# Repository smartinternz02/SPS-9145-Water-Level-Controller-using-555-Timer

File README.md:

# SPS-9145-Water-Level-Controller-using-555-Timer
Water Level Controller using 555 Timer

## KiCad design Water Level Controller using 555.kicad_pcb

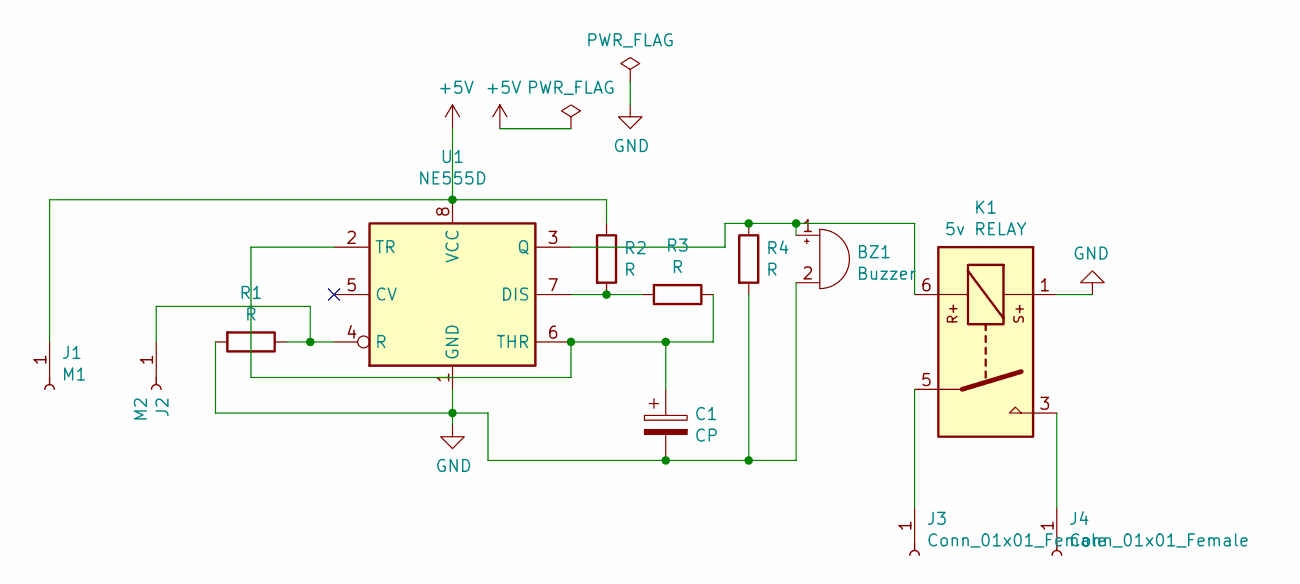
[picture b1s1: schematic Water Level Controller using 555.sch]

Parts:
BZ1: Buzzer; MagneticBuzzer_Kingstate_KCG0601
C1: CP; CP_Radial_D5.0mm_P2.50mm
J1: M1; Banana_Jack_1Pin
J2: M2; Banana_Jack_1Pin
J3, J4: Conn_01x01_Female; Banana_Jack_1Pin
K1: 5v RELAY; Relay_1P1T_NO_10x24x18.8mm_Panasonic_ADW11xxxxW_THT
R1, R2, R3, R4: R; R_Axial_DIN0207_L6.3mm_D2.5mm_P10.16mm_Horizontal
U1: NE555D; SOIC-8_3.9x4.9mm_P1.27mm

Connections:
+5V: J1.1, R2.1, U1.8 (VCC)
GND: BZ1.2 (+), C1.2, K1.1, R1.2, R4.2, U1.1 (GND)
unnamed: BZ1.1 (-), K1.6, R4.1, U1.3 (Q)
unnamed: C1.1, R3.1, U1.2 (TR), U1.6 (THR)
unnamed: J2.1, R1.1, U1.4 (R)
unnamed: J3.1, K1.5
unnamed: J4.1, K1.3
unnamed: R2.2, R3.2, U1.7 (DIS)

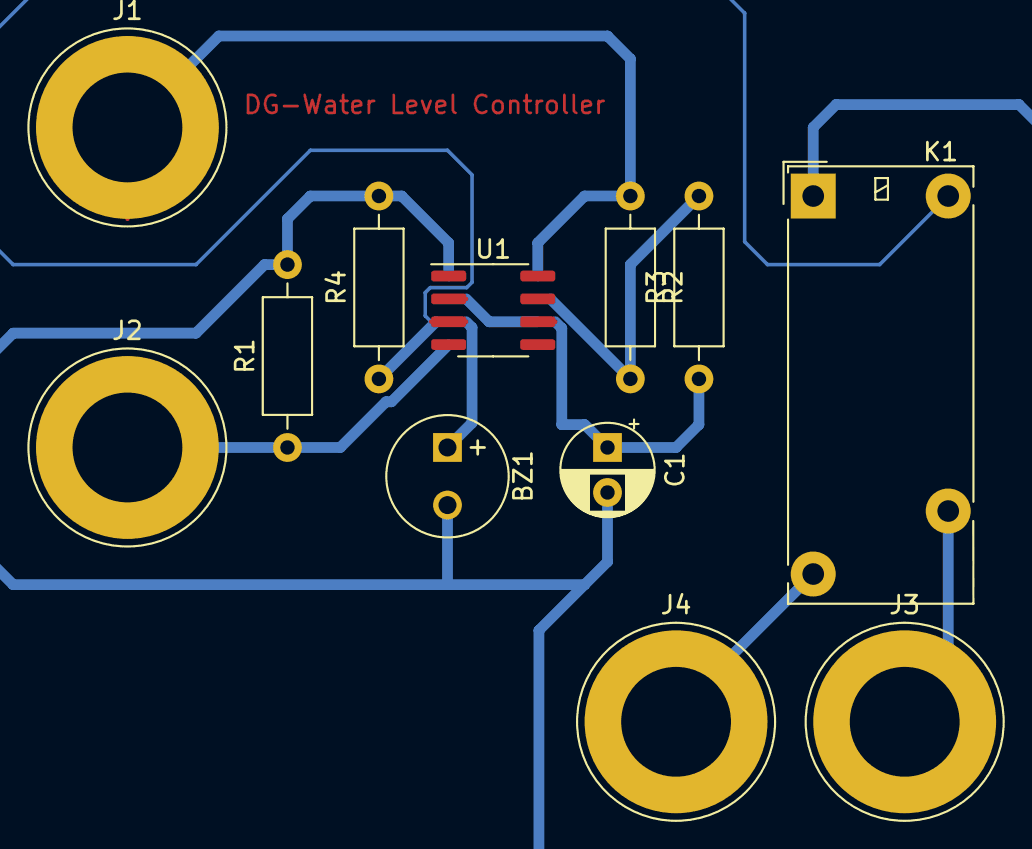
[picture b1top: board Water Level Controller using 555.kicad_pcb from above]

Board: 2 copper layers, 12 parts (0 on the bottom side), 8 nets.
